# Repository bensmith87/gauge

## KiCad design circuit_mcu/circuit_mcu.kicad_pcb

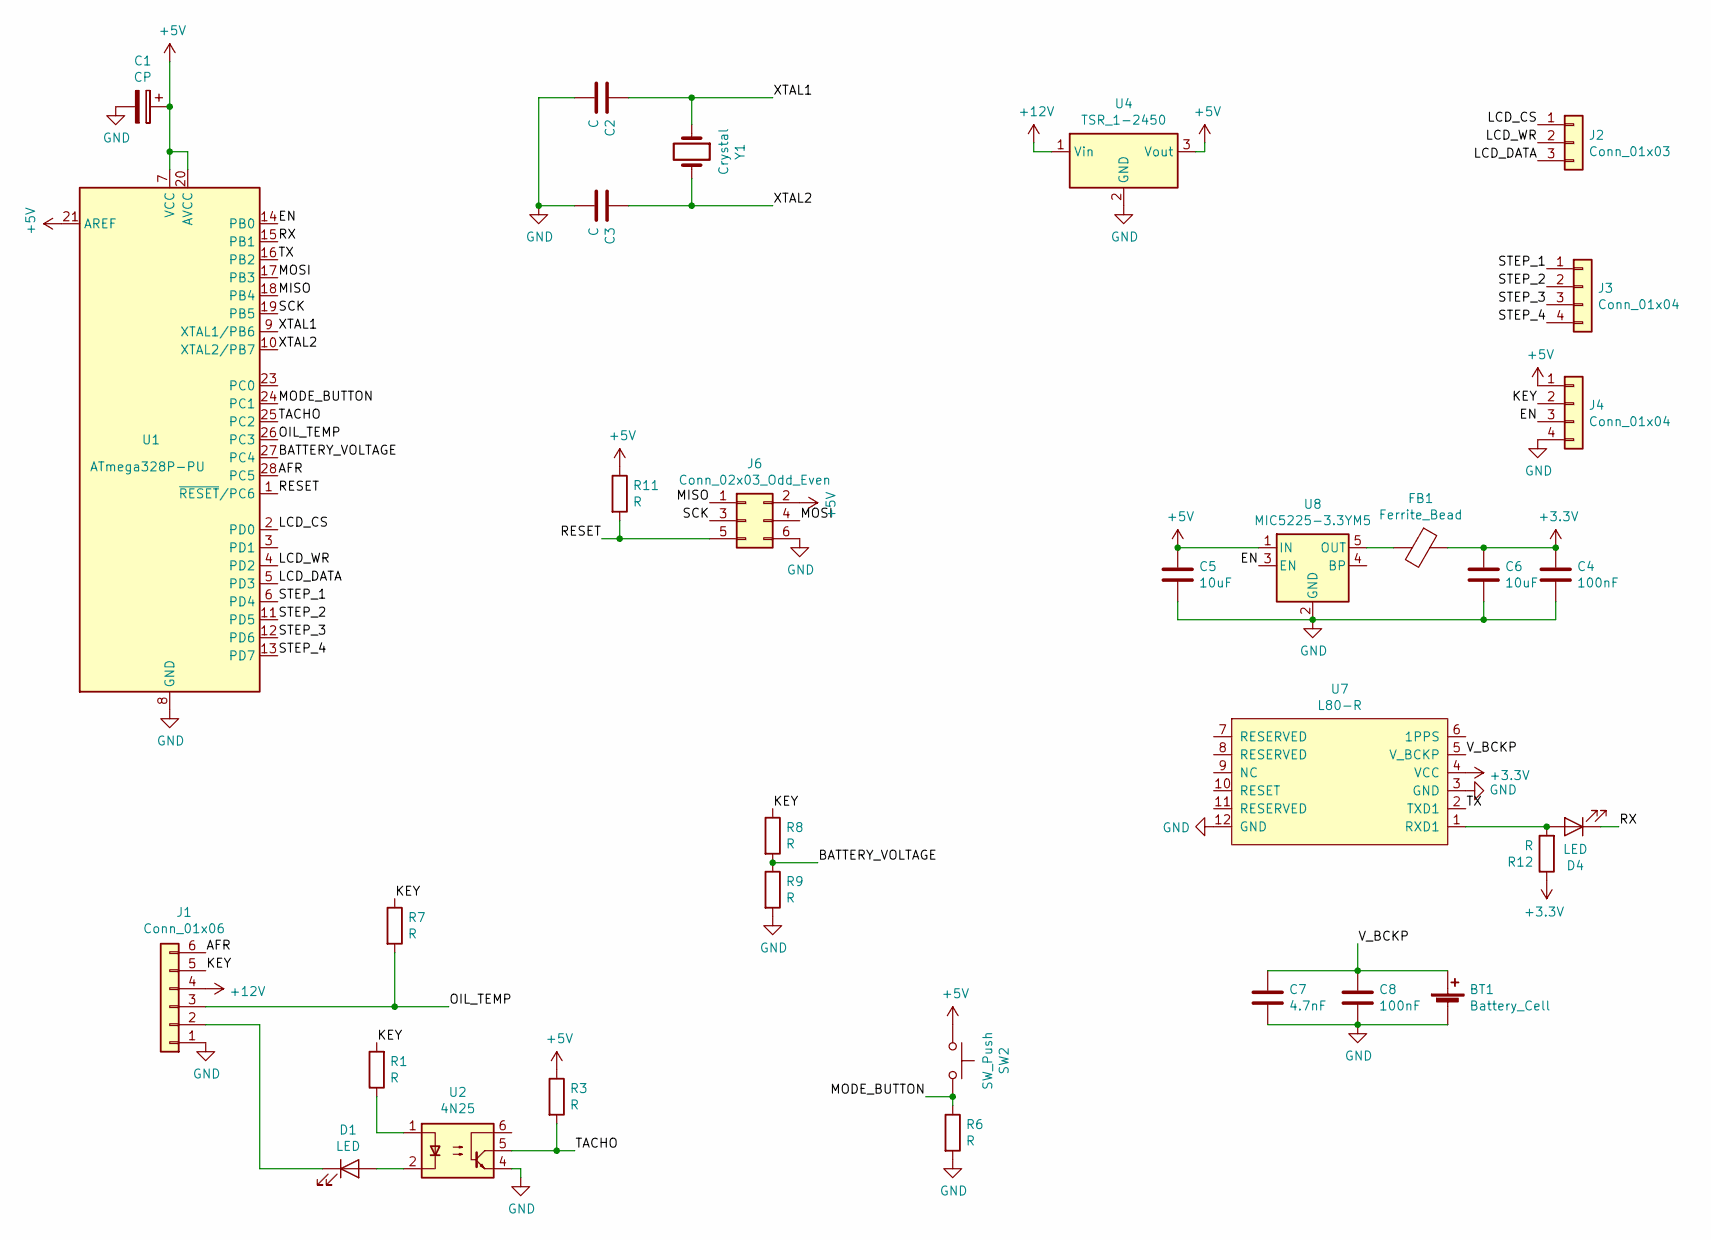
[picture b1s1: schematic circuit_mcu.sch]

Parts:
BT1: Battery_Cell; Coin Battery Holder
C1: CP; CP_Radial_D4.0mm_P1.50mm
C2, C3: C; C_1206_3216Metric
C4, C8: 100nF; C_1206_3216Metric
C5, C6: 10uF; C_1206_3216Metric
C7: 4.7nF; C_1206_3216Metric
D1, D4: LED; LED_1206_3216Metric
FB1: Ferrite_Bead; L_1206_3216Metric
J1: Conn_01x06; PinSocket_1x06_P2.54mm_Vertical
J2: Conn_01x03; PinSocket_1x03_P2.54mm_Vertical
J3, J4: Conn_01x04; PinSocket_1x04_P2.54mm_Vertical
J6: Conn_02x03_Odd_Even; PinHeader_2x03_P2.54mm_Vertical
R1, R3, R6, R7, R8, R9, R11, R12: R; R_1206_3216Metric
SW2: SW_Push; PinSocket_1x02_P2.54mm_Vertical
U1: ATmega328P-PU; DIP-28_W7.62mm
U2: 4N25; DIP-6_W7.62mm
U4: TSR_1-2450; Converter_DCDC_TRACO_TSR-1_THT
U7: L80-R
U8: MIC5225-3.3YM5; SOT-23-5
Y1: Crystal; Resonator-2Pin_W7.0mm_H2.5mm

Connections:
+3V3: C4.2, C6.2, FB1.1, R12.1, U7.4 (VCC)
+5V: C1.1, C5.2, J4.1, J6.2, R3.1, R11.1, SW2.1, U1.7 (VCC), U1.20 (AVCC), U1.21 (AREF), U4.3 (Vout), U8.1 (IN)
+12V: J1.4, U4.1 (Vin)
/AFR: J1.6, U1.28 (PC5)
/BATTERY_VOLTAGE: R8.2, R9.1, U1.27 (PC4)
/EN: J4.3, U1.14 (PB0), U8.3 (EN)
/KEY: J1.5, J4.2, R1.2, R7.1, R8.1
/LCD_CS: J2.1, U1.2 (PD0)
/LCD_DATA: J2.3, U1.5 (PD3)
/LCD_WR: J2.2, U1.4 (PD2)
/MISO: J6.1, U1.18 (PB4)
/MODE_BUTTON: R6.1, SW2.2, U1.24 (PC1)
/MOSI: J6.4, U1.17 (PB3)
/OIL_TEMP: J1.3, R7.2, U1.26 (PC3)
/RESET: J6.5, R11.2, U1.1 (~RESET~/PC6)
/RX: D4.1 (K), U1.15 (PB1)
/SCK: J6.3, U1.19 (PB5)
/STEP_1: J3.1, U1.6 (PD4)
/STEP_2: J3.2, U1.11 (PD5)
/STEP_3: J3.3, U1.12 (PD6)
/STEP_4: J3.4, U1.13 (PD7)
/TACHO: R3.2, U1.25 (PC2), U2.5
/TX: U1.16 (PB2), U7.2 (TXD1)
/V_BCKP: BT1.1 (+), C7.2, C8.2, U7.5 (V_BCKP)
/XTAL1: C2.1, U1.9 (XTAL1/PB6), Y1.1
/XTAL2: C3.1, U1.10 (XTAL2/PB7), Y1.2
GND: BT1.2 (-), C1.2, C2.2, C3.2, C4.1, C5.1, C6.1, C7.1, C8.1, J1.1, J4.4, J6.6, R6.2, R9.2, U1.8 (GND), U1.22 (GND), U2.4, U4.2 (GND), U7.3 (GND), U7.12 (GND), U8.2 (GND)
unnamed: D1.1 (K), J1.2
unnamed: D1.2 (A), U2.2
unnamed: D4.2 (A), R12.2, U7.1 (RXD1)
unnamed: FB1.2, U8.5 (OUT)
unnamed: R1.1, U2.1

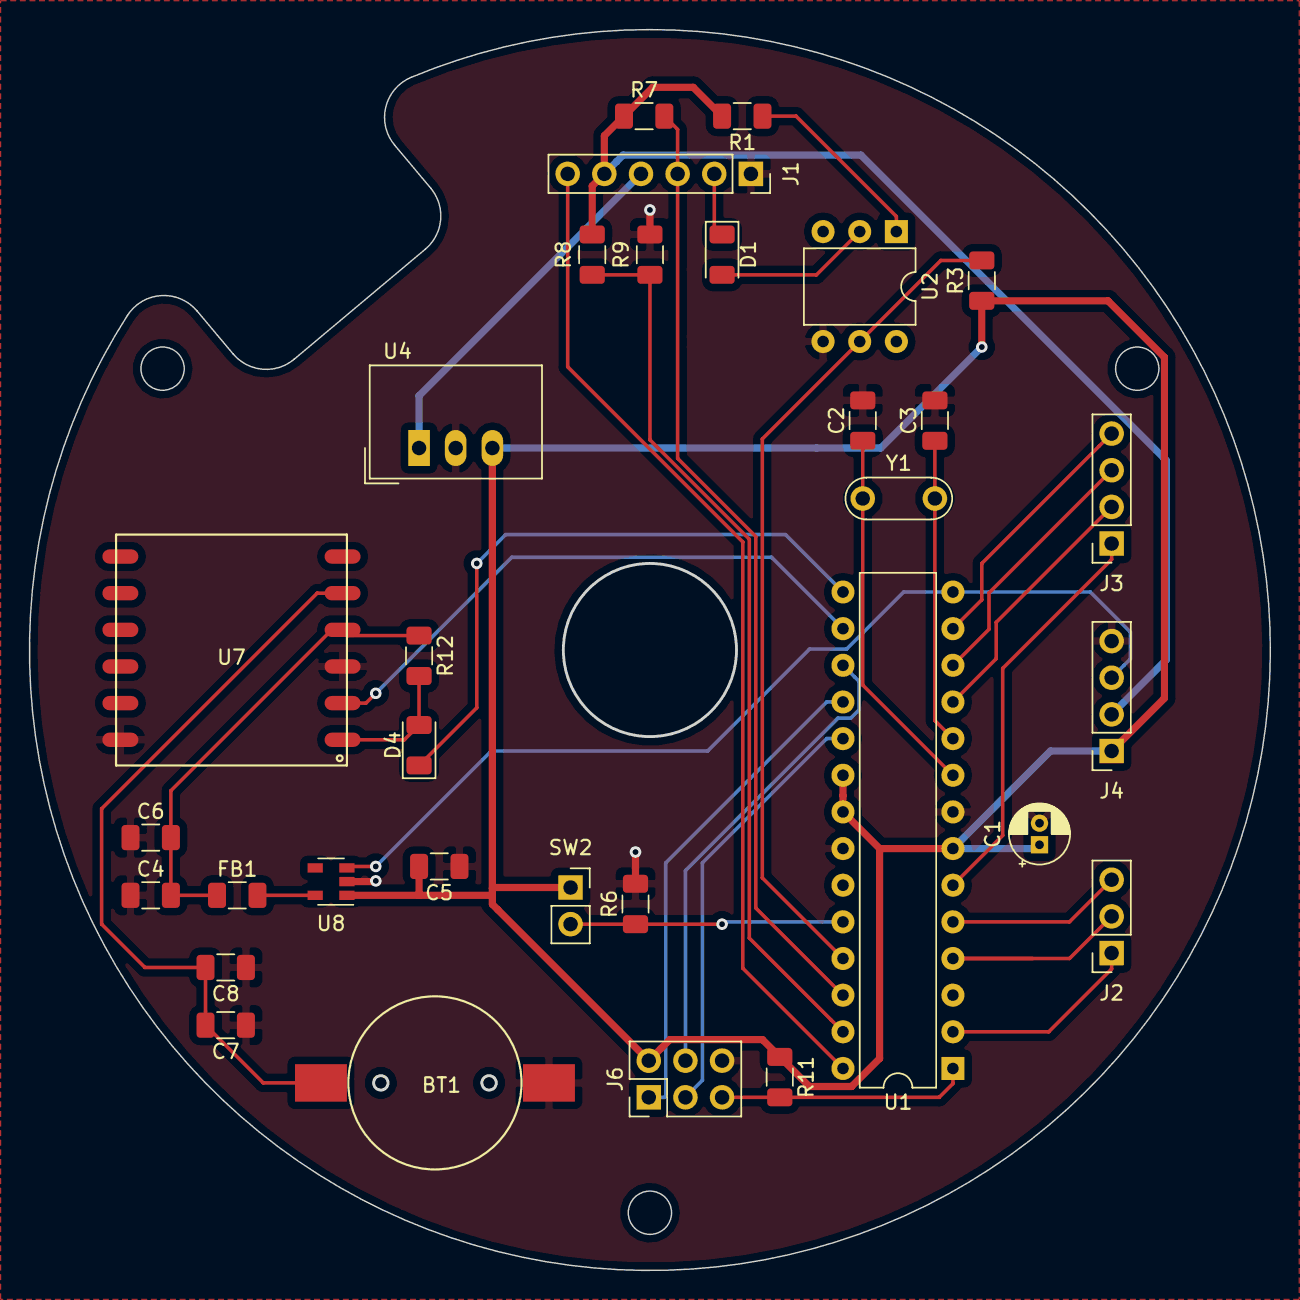
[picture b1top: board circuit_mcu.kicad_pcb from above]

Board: 2 copper layers, 85.9 x 85.9 mm, 32 parts (0 on the bottom side), 32 nets.

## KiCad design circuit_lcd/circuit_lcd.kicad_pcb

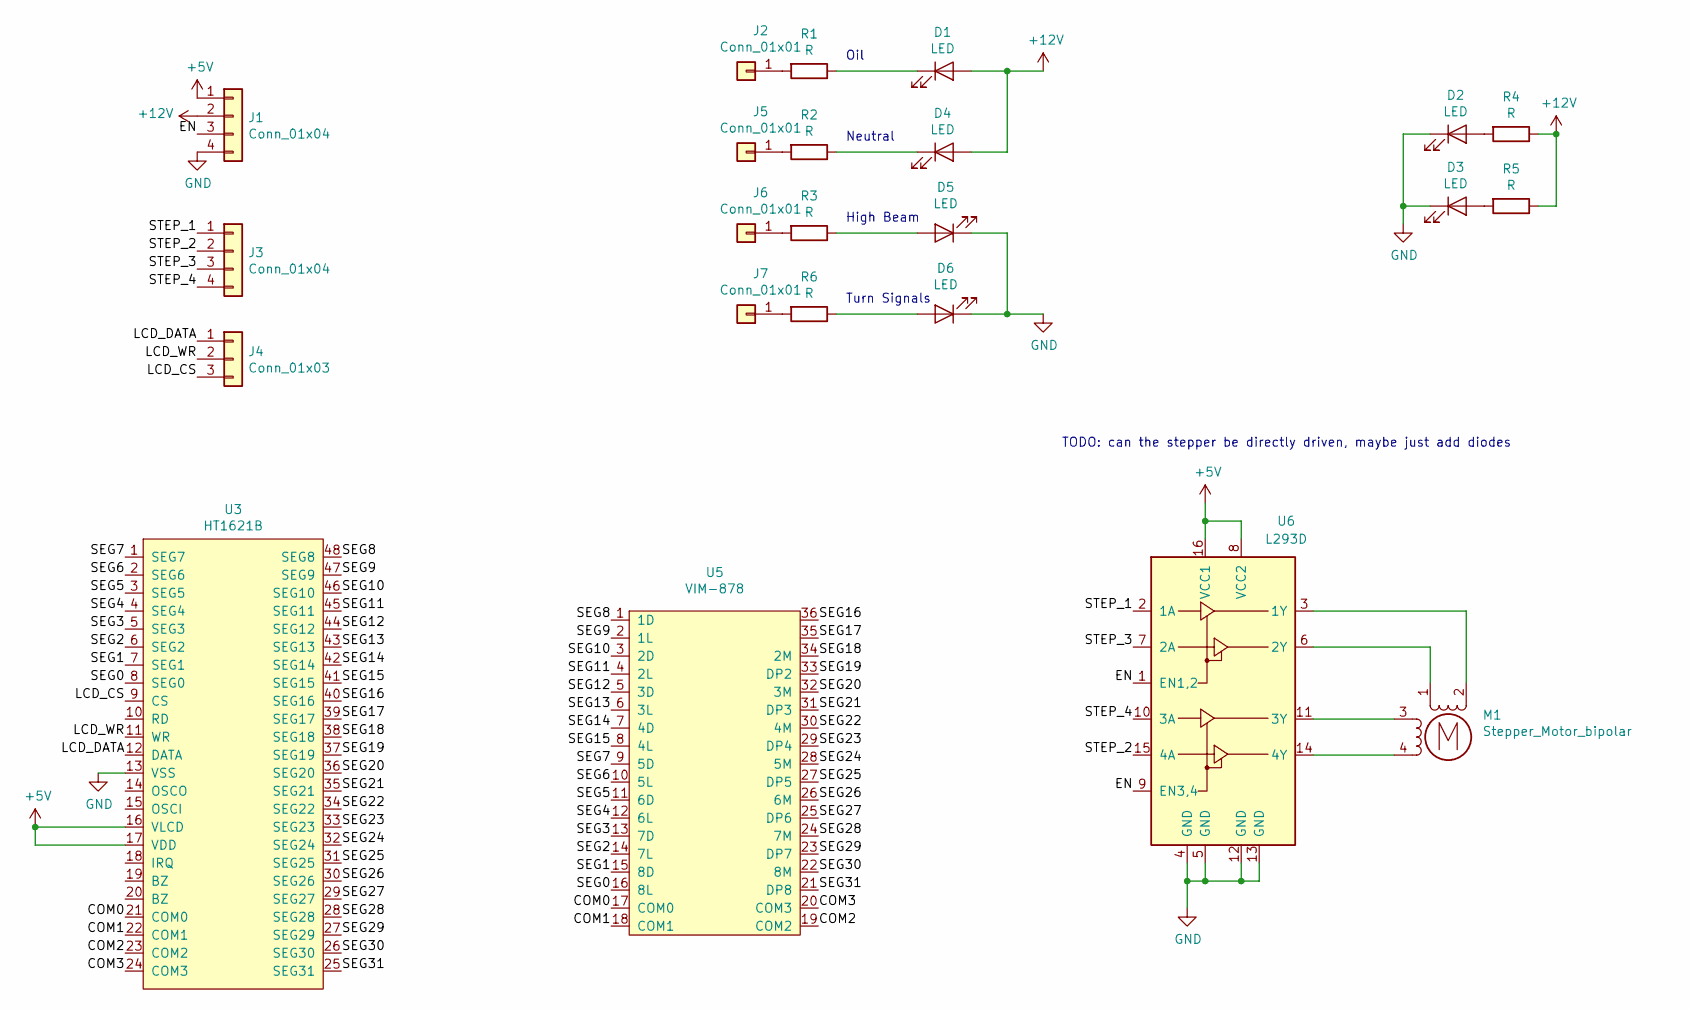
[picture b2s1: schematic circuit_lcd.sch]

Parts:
D1, D4, D5, D6: LED; LED_D5.0mm
D2, D3: LED; LED_1206_3216Metric
J1, J3: Conn_01x04; PinSocket_1x04_P2.54mm_Vertical
J2, J5, J6, J7: Conn_01x01; PinSocket_1x01_P2.54mm_Vertical
J4: Conn_01x03; PinSocket_1x03_P2.54mm_Vertical
M1: Stepper_Motor_bipolar; Stepper Motor
R1, R2, R3, R4, R5, R6: R; R_1206_3216Metric
U3: HT1621B; HT1621
U5: VIM-878; VIM-878-DP
U6: L293D; DIP-16_W7.62mm

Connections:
+5V: J1.1, U3.16 (VLCD), U3.17 (VDD), U6.8 (VCC2), U6.16 (VCC1)
+12V: D1.2 (A), D4.2 (A), J1.2, R4.1, R5.1
/COM0: U3.21 (COM0), U5.17 (COM0)
/COM1: U3.22 (COM1), U5.18 (COM1)
/COM2: U3.23 (COM2), U5.19 (COM2)
/COM3: U3.24 (COM3), U5.20 (COM3)
/EN: J1.3, U6.1 (EN1,2), U6.9 (EN3,4)
/LCD_CS: J4.3, U3.9 (CS)
/LCD_DATA: J4.1, U3.12 (DATA)
/LCD_WR: J4.2, U3.11 (WR)
/SEG0: U3.8 (SEG0), U5.16 (8L)
/SEG1: U3.7 (SEG1), U5.15 (8D)
/SEG2: U3.6 (SEG2), U5.14 (7L)
/SEG3: U3.5 (SEG3), U5.13 (7D)
/SEG4: U3.4 (SEG4), U5.12 (6L)
/SEG5: U3.3 (SEG5), U5.11 (6D)
/SEG6: U3.2 (SEG6), U5.10 (5L)
/SEG7: U3.1 (SEG7), U5.9 (5D)
/SEG8: U3.48 (SEG8), U5.1 (1D)
/SEG9: U3.47 (SEG9), U5.2 (1L)
/SEG10: U3.46 (SEG10), U5.3 (2D)
/SEG11: U3.45 (SEG11), U5.4 (2L)
/SEG12: U3.44 (SEG12), U5.5 (3D)
/SEG13: U3.43 (SEG13), U5.6 (3L)
/SEG14: U3.42 (SEG14), U5.7 (4D)
/SEG15: U3.41 (SEG15), U5.8 (4L)
/SEG16: U3.40 (SEG16), U5.36
/SEG17: U3.39 (SEG17), U5.35
/SEG18: U3.38 (SEG18), U5.34 (2M)
/SEG19: U3.37 (SEG19), U5.33 (DP2)
/SEG20: U3.36 (SEG20), U5.32 (3M)
/SEG21: U3.35 (SEG21), U5.31 (DP3)
/SEG22: U3.34 (SEG22), U5.30 (4M)
/SEG23: U3.33 (SEG23), U5.29 (DP4)
/SEG24: U3.32 (SEG24), U5.28 (5M)
/SEG25: U3.31 (SEG25), U5.27 (DP5)
/SEG26: U3.30 (SEG26), U5.26 (6M)
/SEG27: U3.29 (SEG27), U5.25 (DP6)
/SEG28: U3.28 (SEG28), U5.24 (7M)
/SEG29: U3.27 (SEG29), U5.23 (DP7)
/SEG30: U3.26 (SEG30), U5.22 (8M)
/SEG31: U3.25 (SEG31), U5.21 (DP8)
/STEP_1: J3.1, U6.2 (1A)
/STEP_2: J3.2, U6.15 (4A)
/STEP_3: J3.3, U6.7 (2A)
/STEP_4: J3.4, U6.10 (3A)
GND: D2.1 (K), D3.1 (K), D5.1 (K), D6.1 (K), J1.4, U3.13 (VSS), U6.4 (GND), U6.5 (GND), U6.12 (GND), U6.13 (GND)
unnamed: D1.1 (K), R1.1
unnamed: D2.2 (A), R4.2
unnamed: D3.2 (A), R5.2
unnamed: D4.1 (K), R2.1
unnamed: D5.2 (A), R3.1
unnamed: D6.2 (A), R6.1
unnamed: J2.1, R1.2
unnamed: J5.1, R2.2
unnamed: J6.1, R3.2
unnamed: J7.1, R6.2
unnamed: M1.1, U6.6 (2Y)
unnamed: M1.2 (-), U6.3 (1Y)
unnamed: M1.3, U6.11 (3Y)
unnamed: M1.4, U6.14 (4Y)

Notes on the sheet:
TODO: can the stepper be directly driven, maybe just add diodes
Oil
Neutral
High Beam
Turn Signals

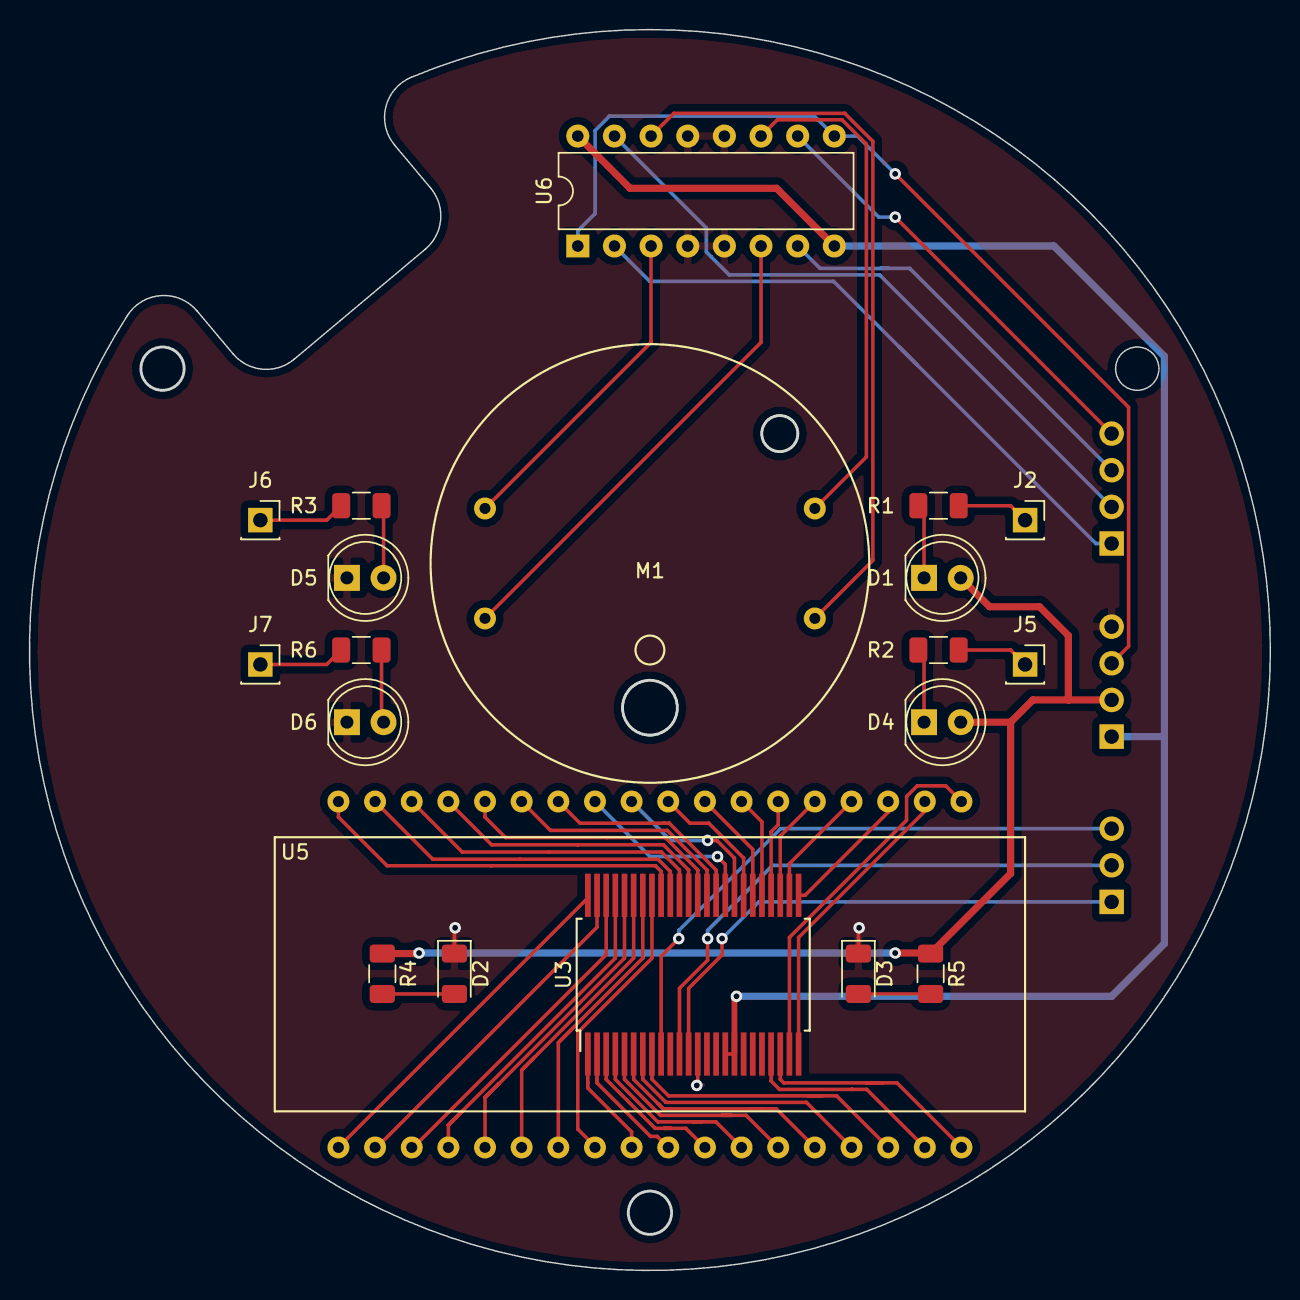
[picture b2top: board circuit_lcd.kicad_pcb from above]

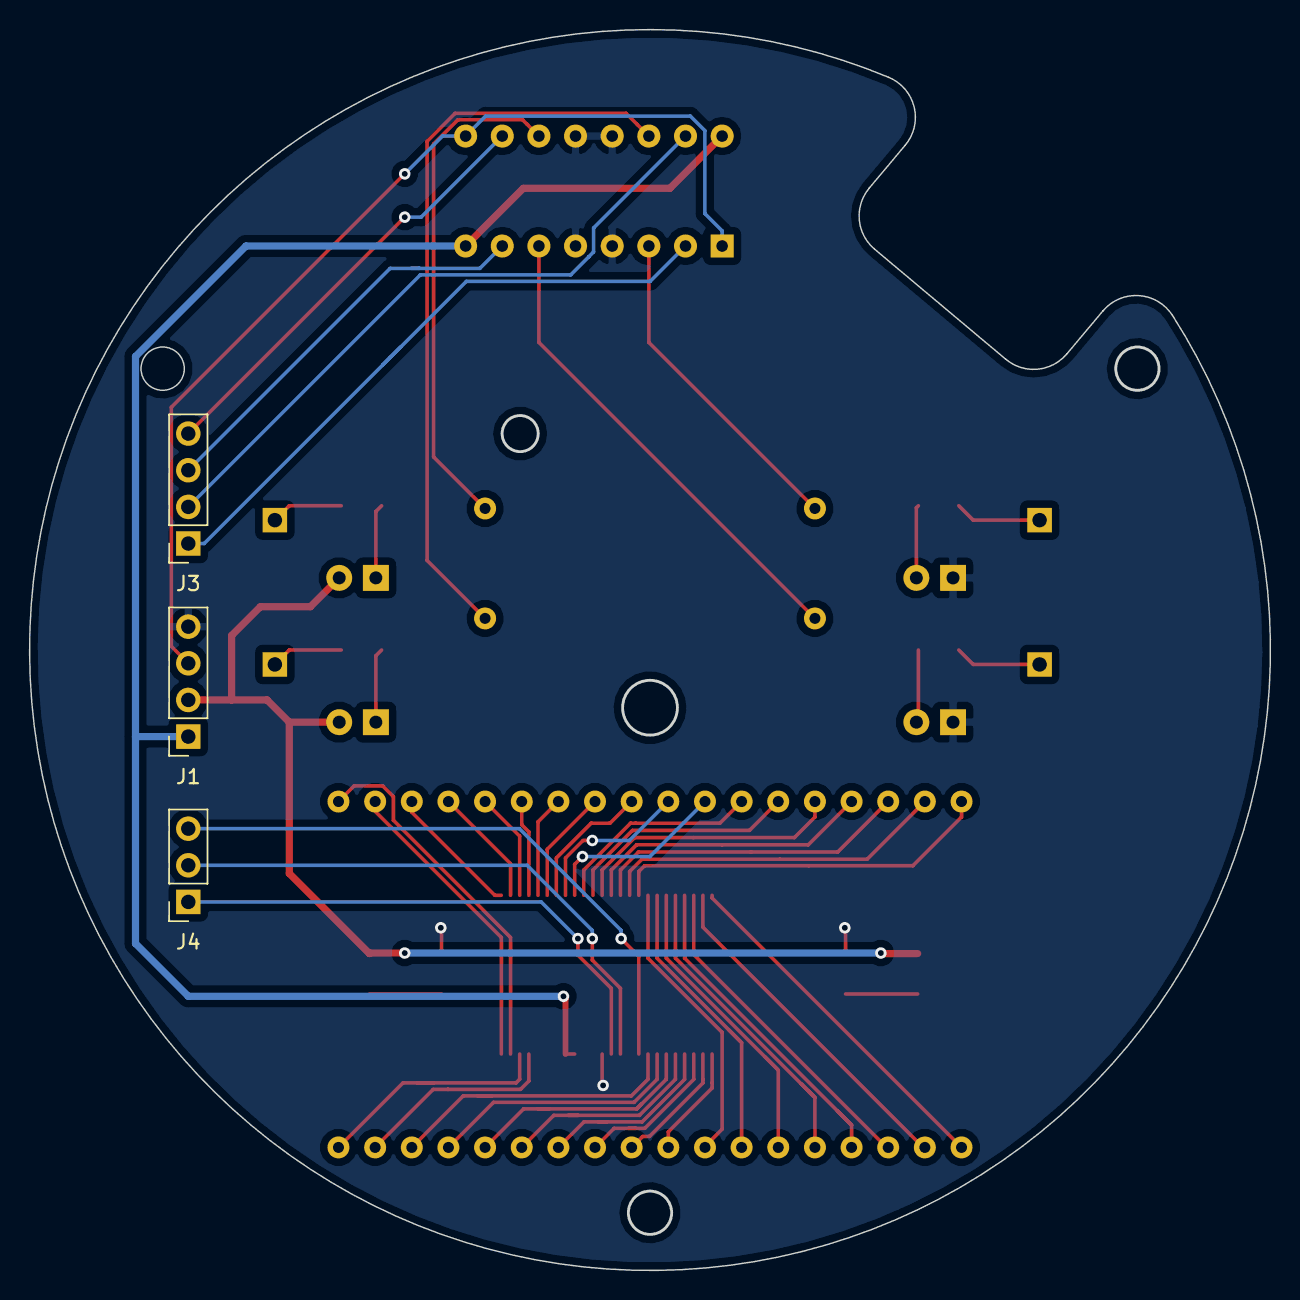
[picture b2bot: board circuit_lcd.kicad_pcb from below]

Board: 2 copper layers, 85.9 x 85.9 mm, 23 parts (3 on the bottom side), 61 nets.

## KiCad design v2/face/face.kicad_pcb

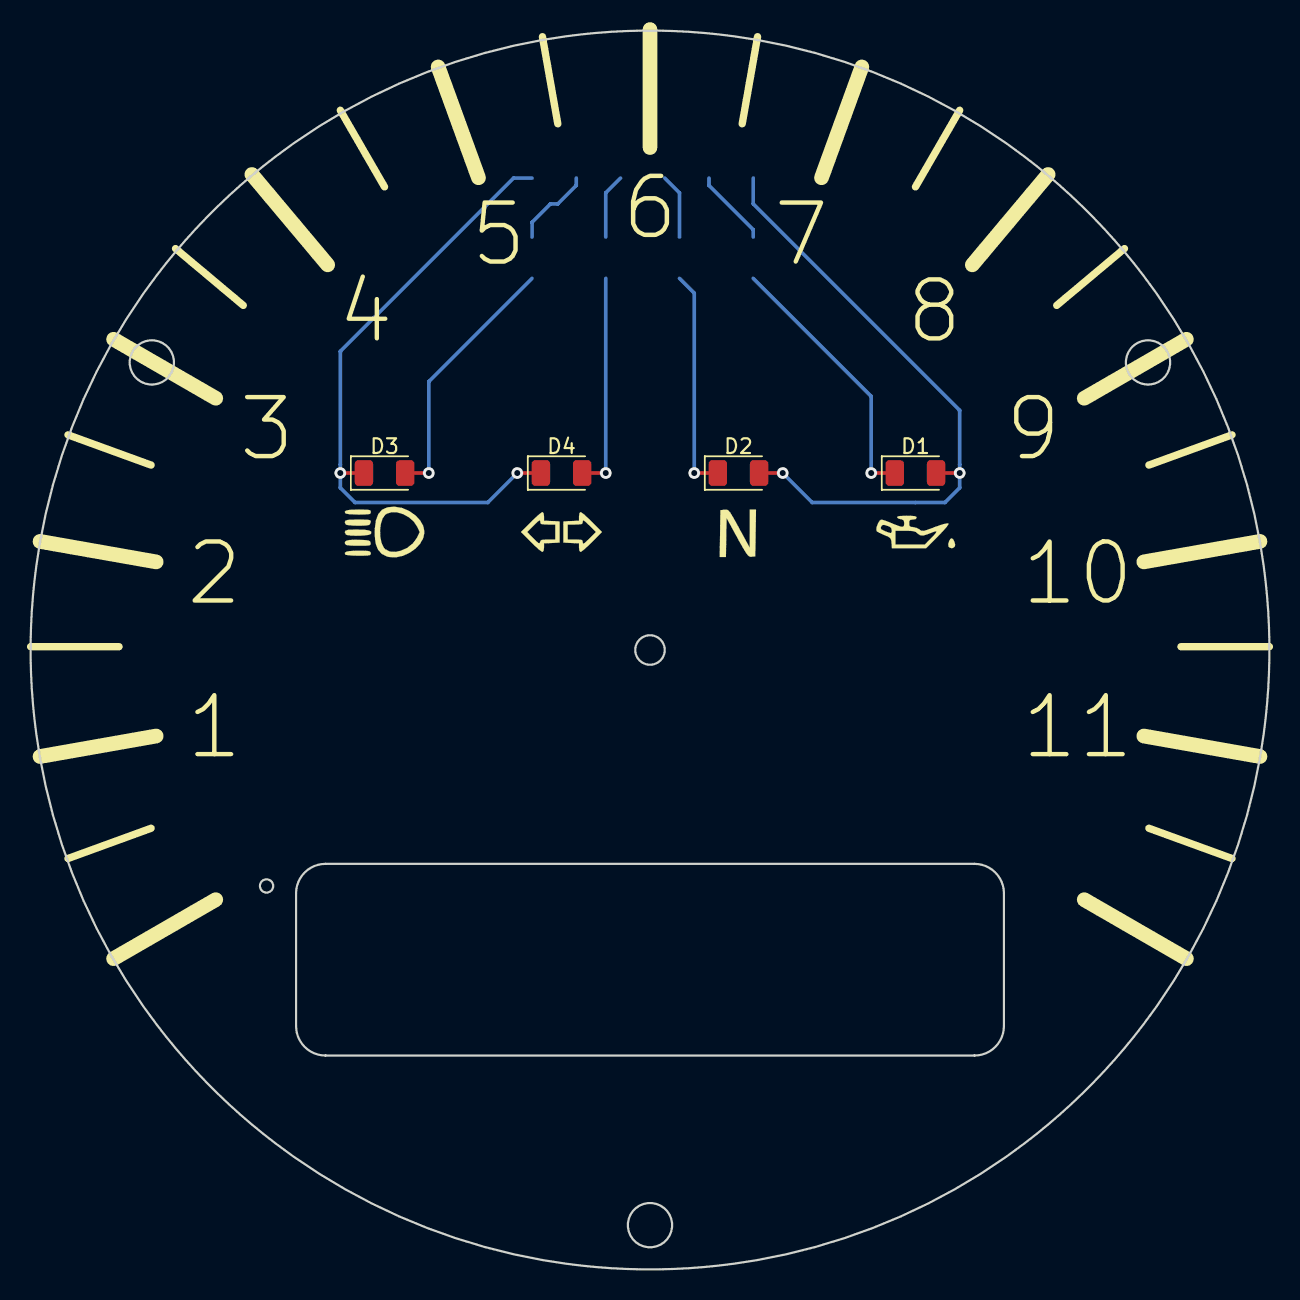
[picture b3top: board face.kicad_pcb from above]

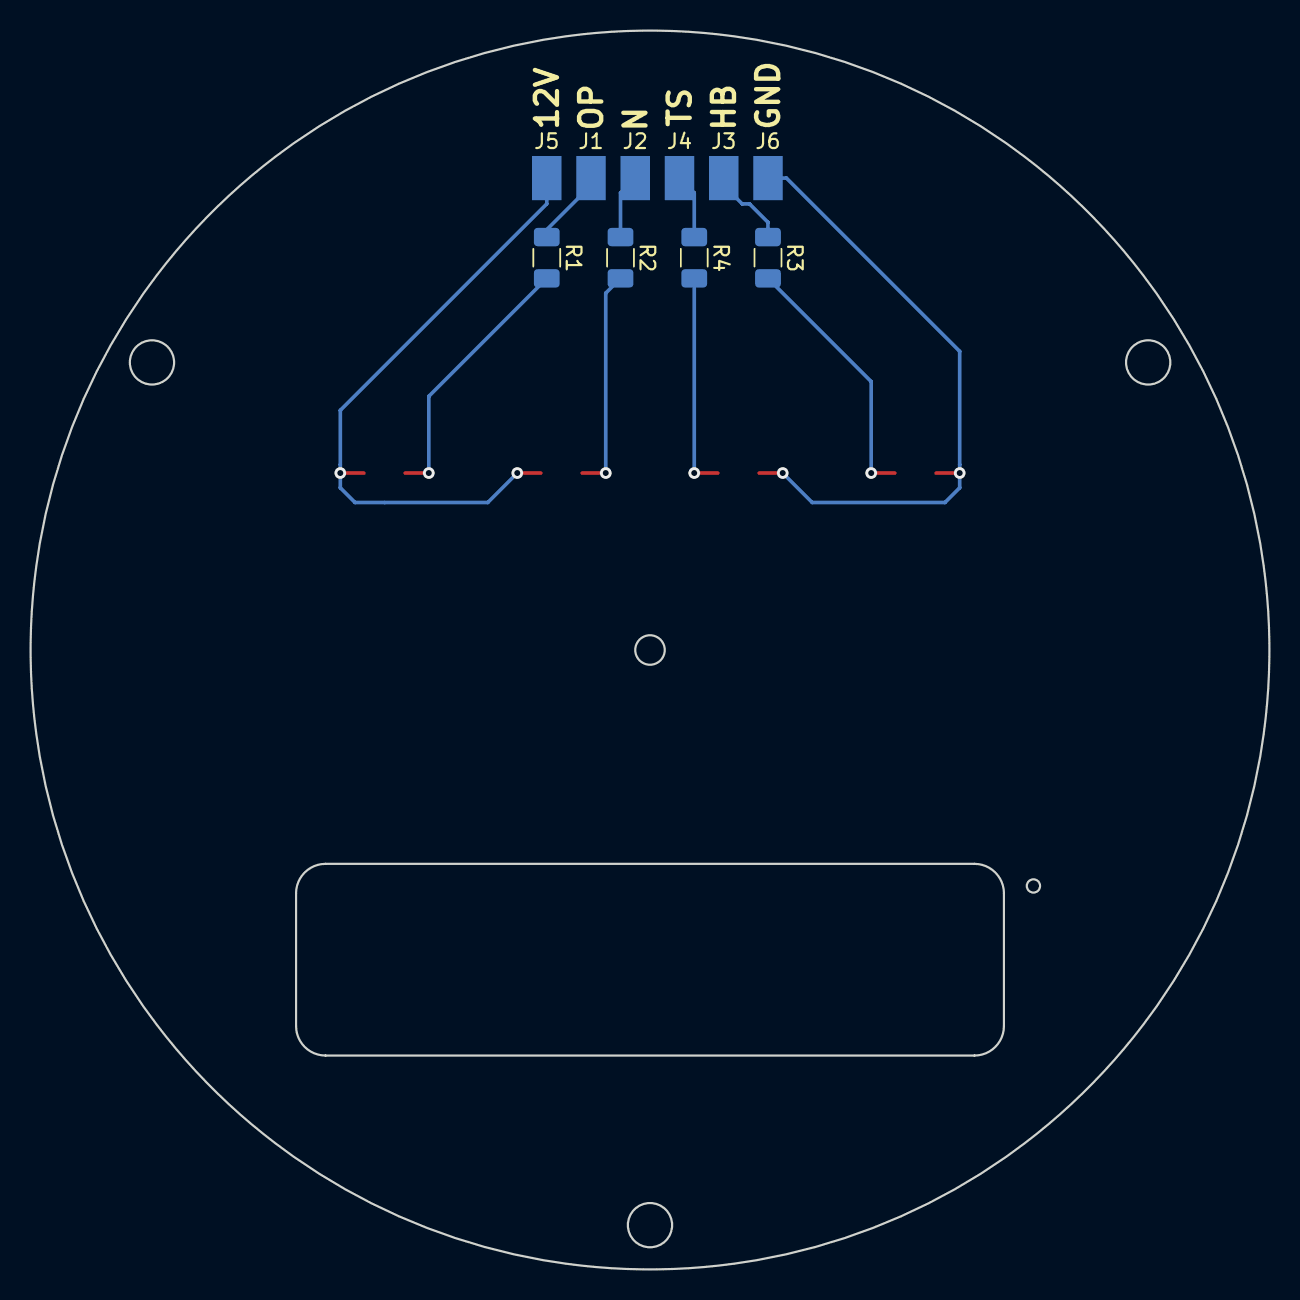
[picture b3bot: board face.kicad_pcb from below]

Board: 2 copper layers, 84.0 x 84.0 mm, 14 parts (10 on the bottom side), 10 nets.

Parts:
D1, D2, D3, D4: LED; LED_1206_3216Metric
J1, J2, J3, J4, J5, J6: Conn_01x01; wire-pad
R1, R2, R3, R4: 220; R_1206_3216Metric

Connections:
+12V: D1.2, D2.2, J5.1
GND: D3.1, D4.1, J6.1
unnamed: D1.1, R1.2
unnamed: D2.1, R2.2
unnamed: D3.2, R3.2
unnamed: D4.2, R4.2
unnamed: J1.1, R1.1
unnamed: J2.1, R2.1
unnamed: J3.1, R3.1
unnamed: J4.1, R4.1

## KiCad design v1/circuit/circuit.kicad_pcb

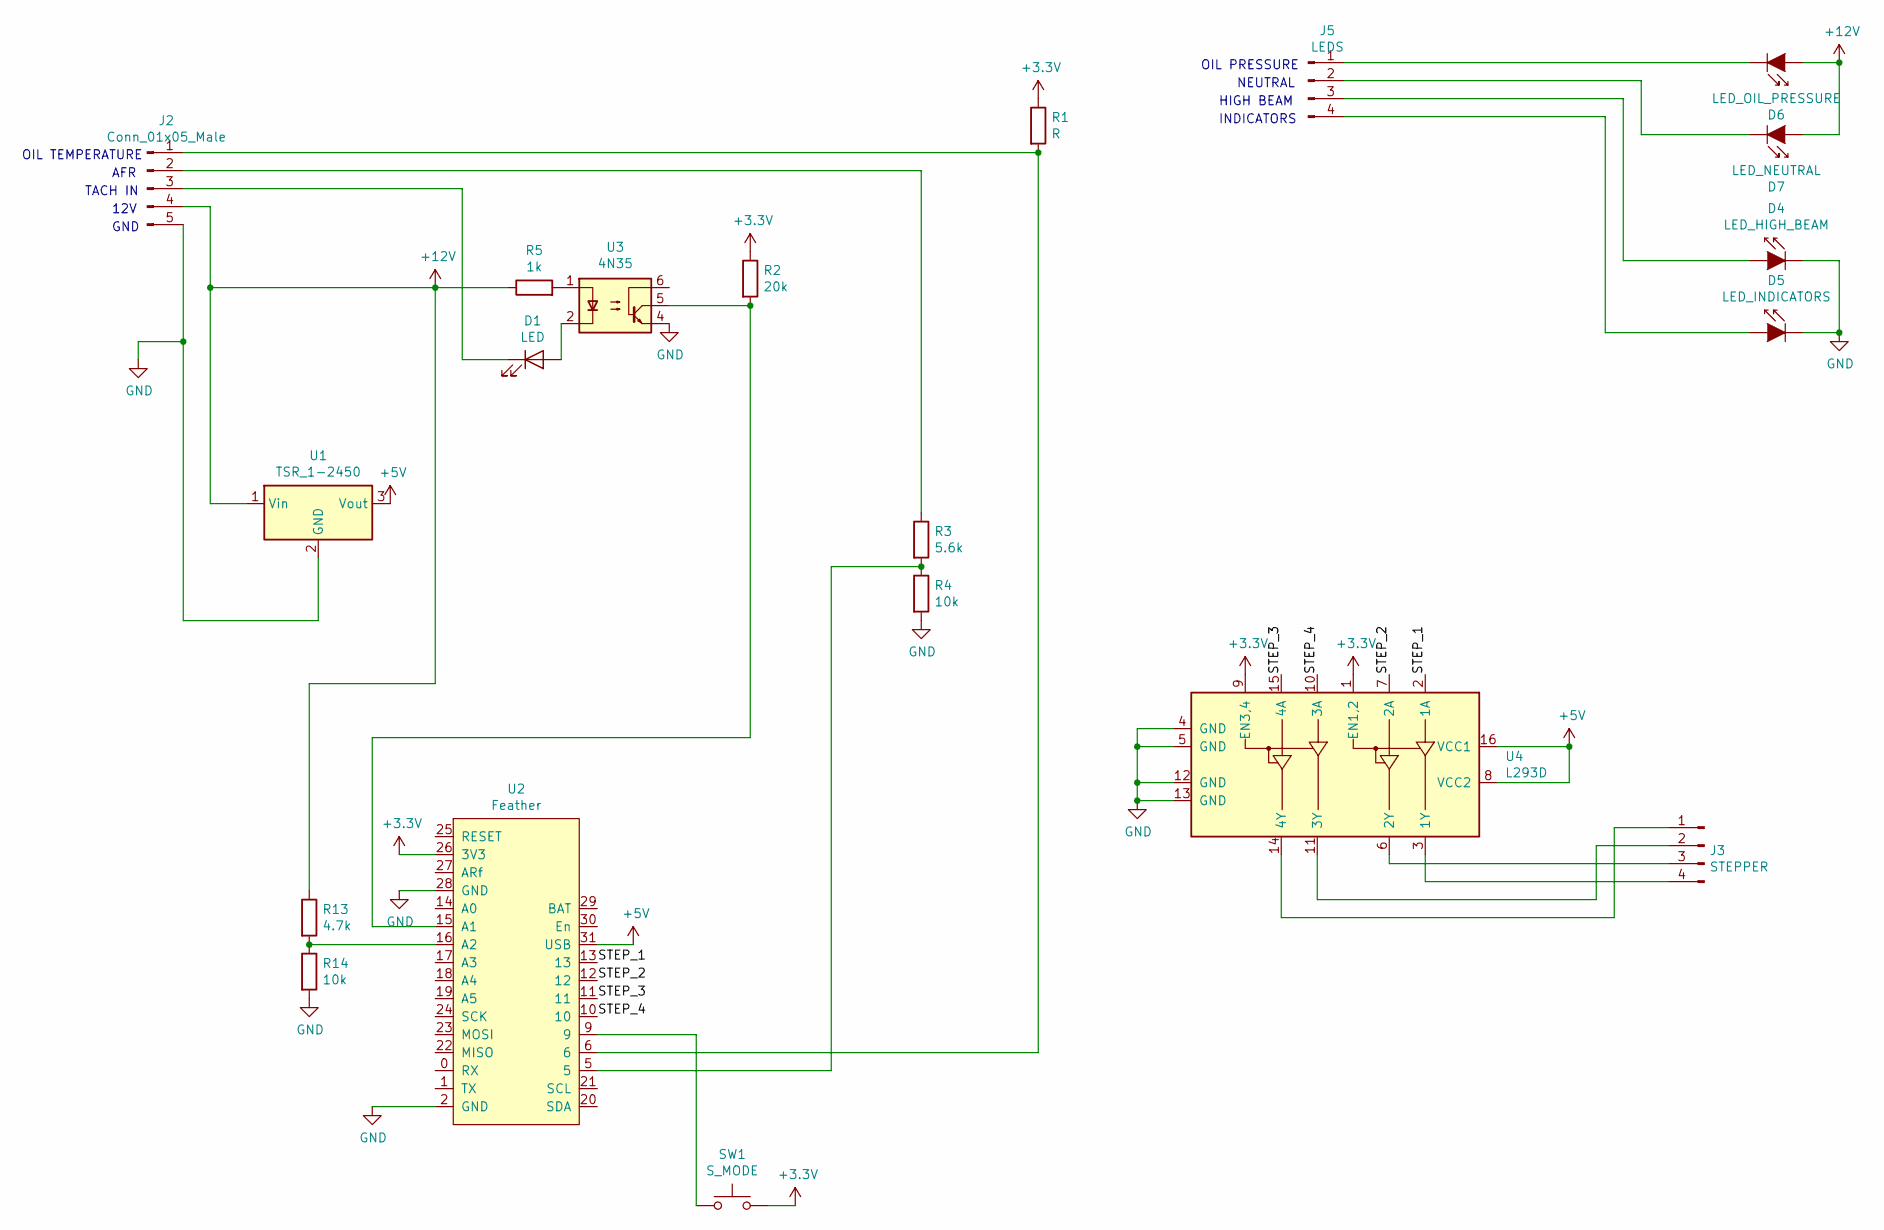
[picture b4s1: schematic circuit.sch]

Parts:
D1: LED; LED_D5.0mm
D4: LED_HIGH_BEAM; PinHeader_1x02_P2.54mm_Vertical
D5: LED_INDICATORS; PinHeader_1x02_P2.54mm_Vertical
D6: LED_OIL_PRESSURE; PinHeader_1x02_P2.54mm_Vertical
D7: LED_NEUTRAL; PinHeader_1x02_P2.54mm_Vertical
J2: Conn_01x05_Male; PinHeader_1x05_P2.54mm_Vertical
J3: STEPPER; PinHeader_1x04_P2.54mm_Vertical
J5: LEDS; PinHeader_1x04_P2.54mm_Vertical
R1: R; R_Axial_DIN0207_L6.3mm_D2.5mm_P10.16mm_Horizontal
R2: 20k; R_Axial_DIN0207_L6.3mm_D2.5mm_P10.16mm_Horizontal
R3: 5.6k; R_Axial_DIN0207_L6.3mm_D2.5mm_P10.16mm_Horizontal
R4, R14: 10k; R_Axial_DIN0207_L6.3mm_D2.5mm_P10.16mm_Horizontal
R5: 1k; R_Axial_DIN0207_L6.3mm_D2.5mm_P10.16mm_Horizontal
R13: 4.7k; R_Axial_DIN0207_L6.3mm_D2.5mm_P10.16mm_Horizontal
SW1: S_MODE; PinHeader_1x02_P2.54mm_Vertical
U1: TSR_1-2450; Converter_DCDC_TRACO_TSR-1_THT
U2: Feather
U3: 4N35; DIP-6_W7.62mm
U4: L293D; DIP-16_W7.62mm

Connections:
+3V3: R1.1, R2.1, SW1.2, U2.26 (3V3), U4.1 (EN1,2), U4.9 (EN3,4)
+5V: U1.3 (Vout), U2.31 (USB), U4.8 (VCC2), U4.16 (VCC1)
+12V: D6.2 (A), D7.2 (A), J2.4, R5.1, R13.1, U1.1 (Vin)
/STEP_1: U2.13, U4.2 (1A)
/STEP_2: U2.12, U4.7 (2A)
/STEP_3: U2.11, U4.15 (4A)
/STEP_4: U2.10, U4.10 (3A)
GND: D4.1 (K), D5.1 (K), J2.5, R4.2, R14.2, U1.2 (GND), U2.2 (GND), U2.28 (GND), U3.4, U4.4 (GND), U4.5 (GND), U4.12 (GND), U4.13 (GND)
unnamed: D1.1 (K), J2.3
unnamed: D1.2 (A), U3.2
unnamed: D4.2 (A), J5.3
unnamed: D5.2 (A), J5.4
unnamed: D6.1 (K), J5.1
unnamed: D7.1 (K), J5.2
unnamed: J2.1, R1.2, U2.6
unnamed: J2.2, R3.1
unnamed: J3.1, U4.14 (4Y)
unnamed: J3.2, U4.11 (3Y)
unnamed: J3.3, U4.6 (2Y)
unnamed: J3.4, U4.3 (1Y)
unnamed: R2.2, U2.15 (A1), U3.5
unnamed: R3.2, R4.1, U2.5
unnamed: R5.2, U3.1
unnamed: R13.2, R14.1, U2.16 (A2)
unnamed: SW1.1, U2.9

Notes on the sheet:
TACH IN
12V
GND
OIL PRESSURE
NEUTRAL
HIGH BEAM
INDICATORS
AFR
OIL TEMPERATURE

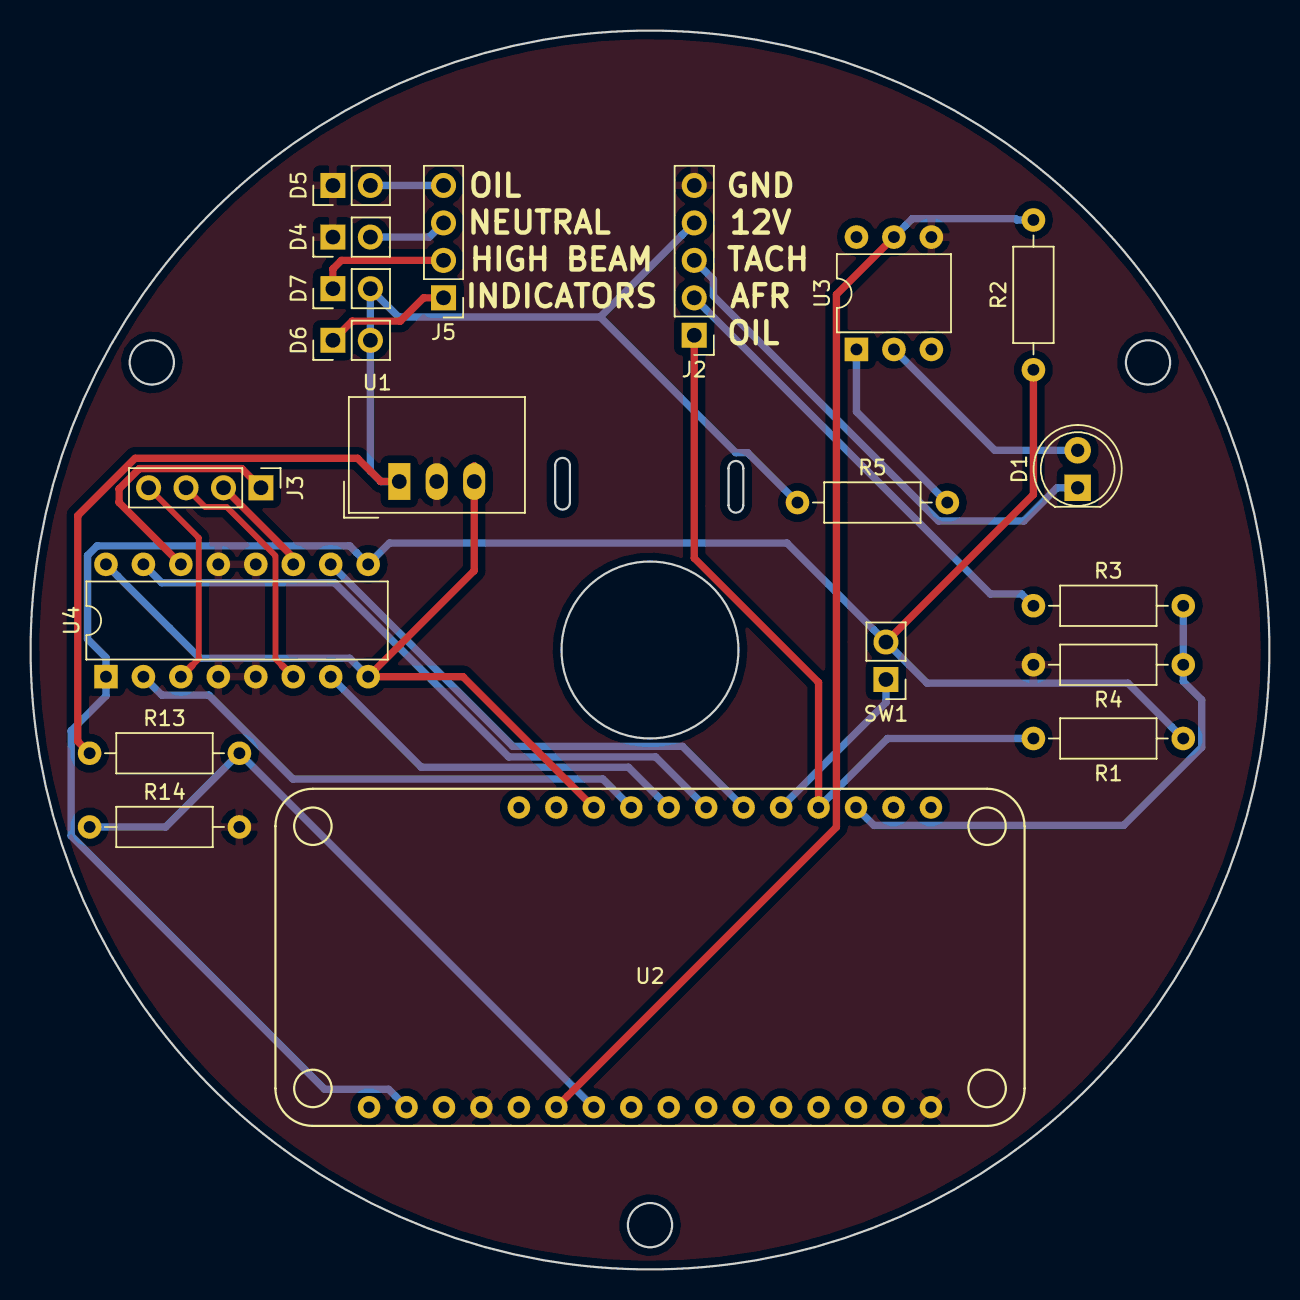
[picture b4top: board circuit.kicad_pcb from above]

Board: 2 copper layers, 84.0 x 84.0 mm, 20 parts (0 on the bottom side), 25 nets.
